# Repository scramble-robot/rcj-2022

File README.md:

# rcj-2022

This program made by scramble rcj team.

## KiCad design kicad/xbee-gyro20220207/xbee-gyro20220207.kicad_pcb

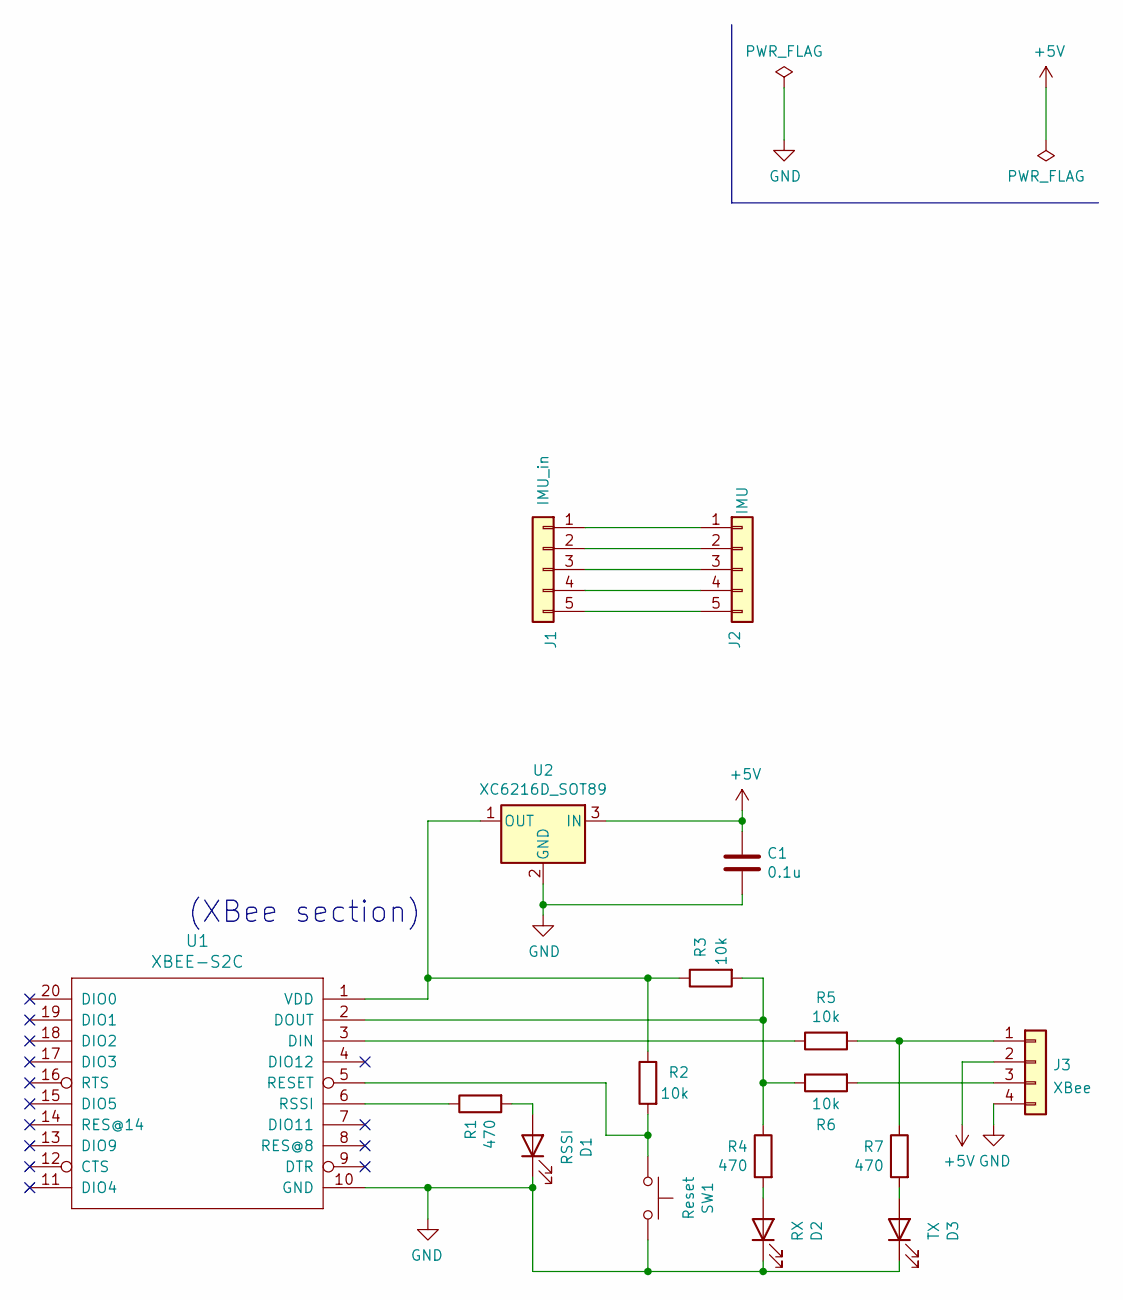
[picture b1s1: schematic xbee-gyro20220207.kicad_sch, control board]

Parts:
C1: 0.1u; C_0603_1608Metric_Pad1.08x0.95mm_HandSolder
D1: RSSI; LED_0603_1608Metric_Pad1.05x0.95mm_HandSolder
D2: RX; LED_0603_1608Metric_Pad1.05x0.95mm_HandSolder
D3: TX; LED_0603_1608Metric_Pad1.05x0.95mm_HandSolder
J1: IMU_in; PinSocket_1x05_P2.54mm_Vertical
J2: IMU; PinSocket_1x05_P2.54mm_Vertical
J3: XBee; PinSocket_1x04_P2.54mm_Vertical
R1, R4, R7: 470; R_0603_1608Metric_Pad0.98x0.95mm_HandSolder
R2, R3, R5, R6: 10k; R_0603_1608Metric_Pad0.98x0.95mm_HandSolder
SW1: Reset; THAU13-AB-R
U1: XBEE-S2C
U2: XC6216D_SOT89; SOT-89-3

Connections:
+5V: C1.1, J3.2, U2.3 (IN)
GND: C1.2, D1.1 (K), D2.1 (K), D3.1 (K), J3.4, SW1.2, U1.10 (GND), U2.2 (GND)
unnamed: D1.2 (A), R1.2
unnamed: D2.2 (A), R4.2
unnamed: D3.2 (A), R7.2
unnamed: J1.1, J2.1
unnamed: J1.2, J2.2
unnamed: J1.3, J2.3
unnamed: J1.4, J2.4
unnamed: J1.5, J2.5
unnamed: J3.1, R5.2, R7.1
unnamed: J3.3, R6.2
unnamed: R1.1, U1.6 (RSSI)
unnamed: R2.1, R3.1, U1.1 (VDD), U2.1 (OUT)
unnamed: R2.2, SW1.1, U1.5 (RESET)
unnamed: R3.2, R4.1, R6.1, U1.2 (DOUT)
unnamed: R5.1, U1.3 (DIN)

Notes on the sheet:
(XBee section)

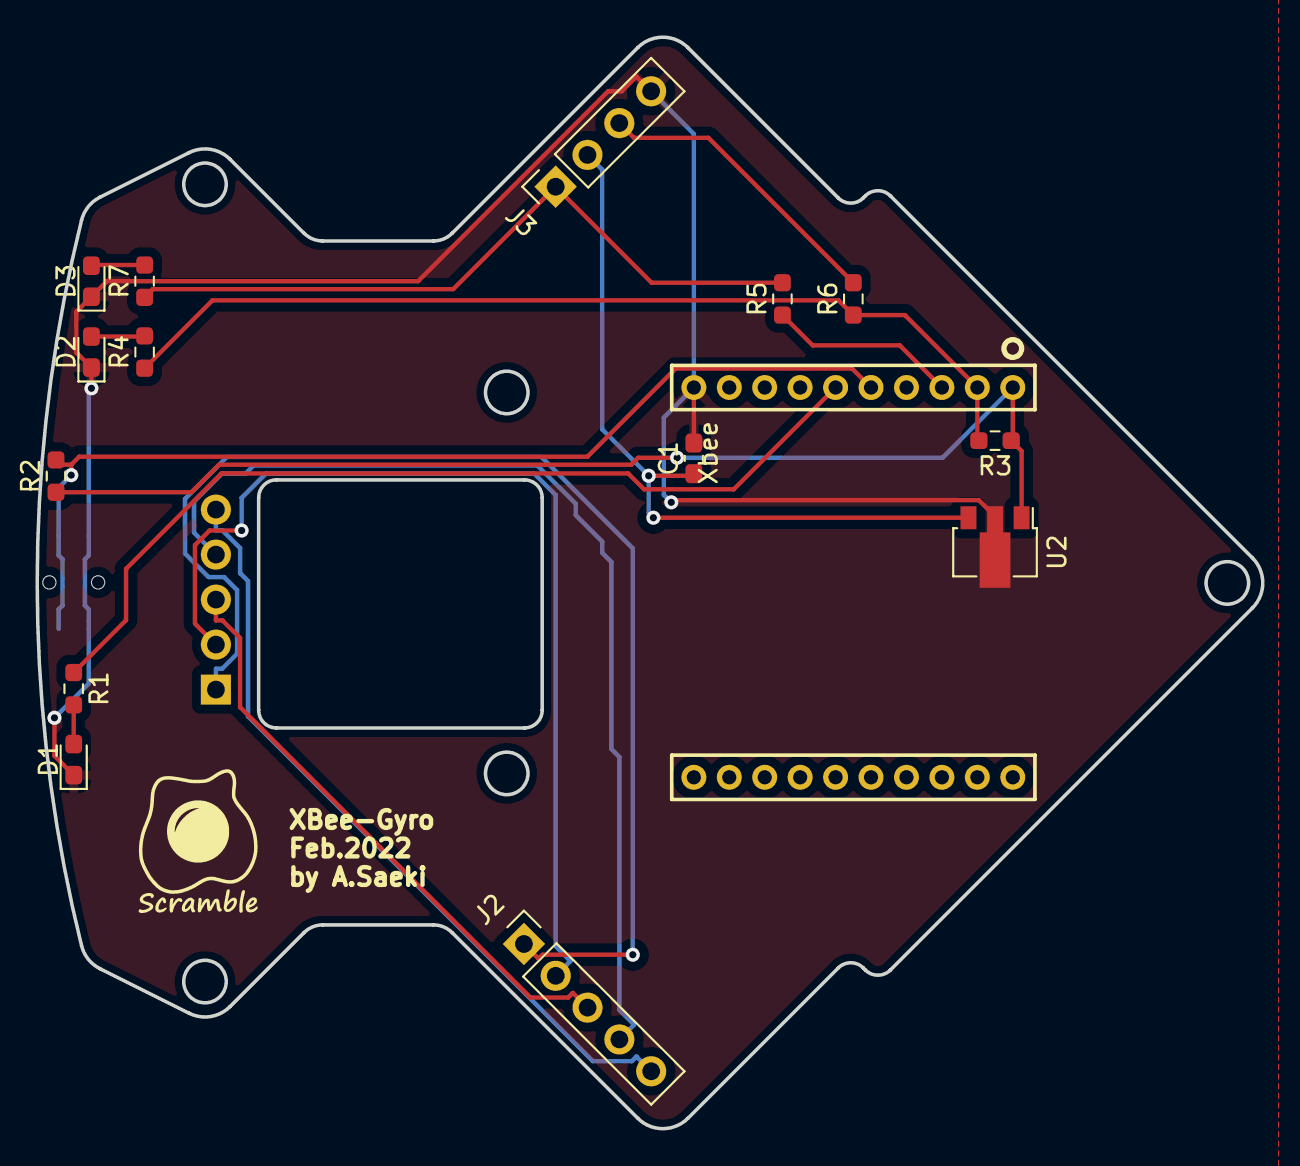
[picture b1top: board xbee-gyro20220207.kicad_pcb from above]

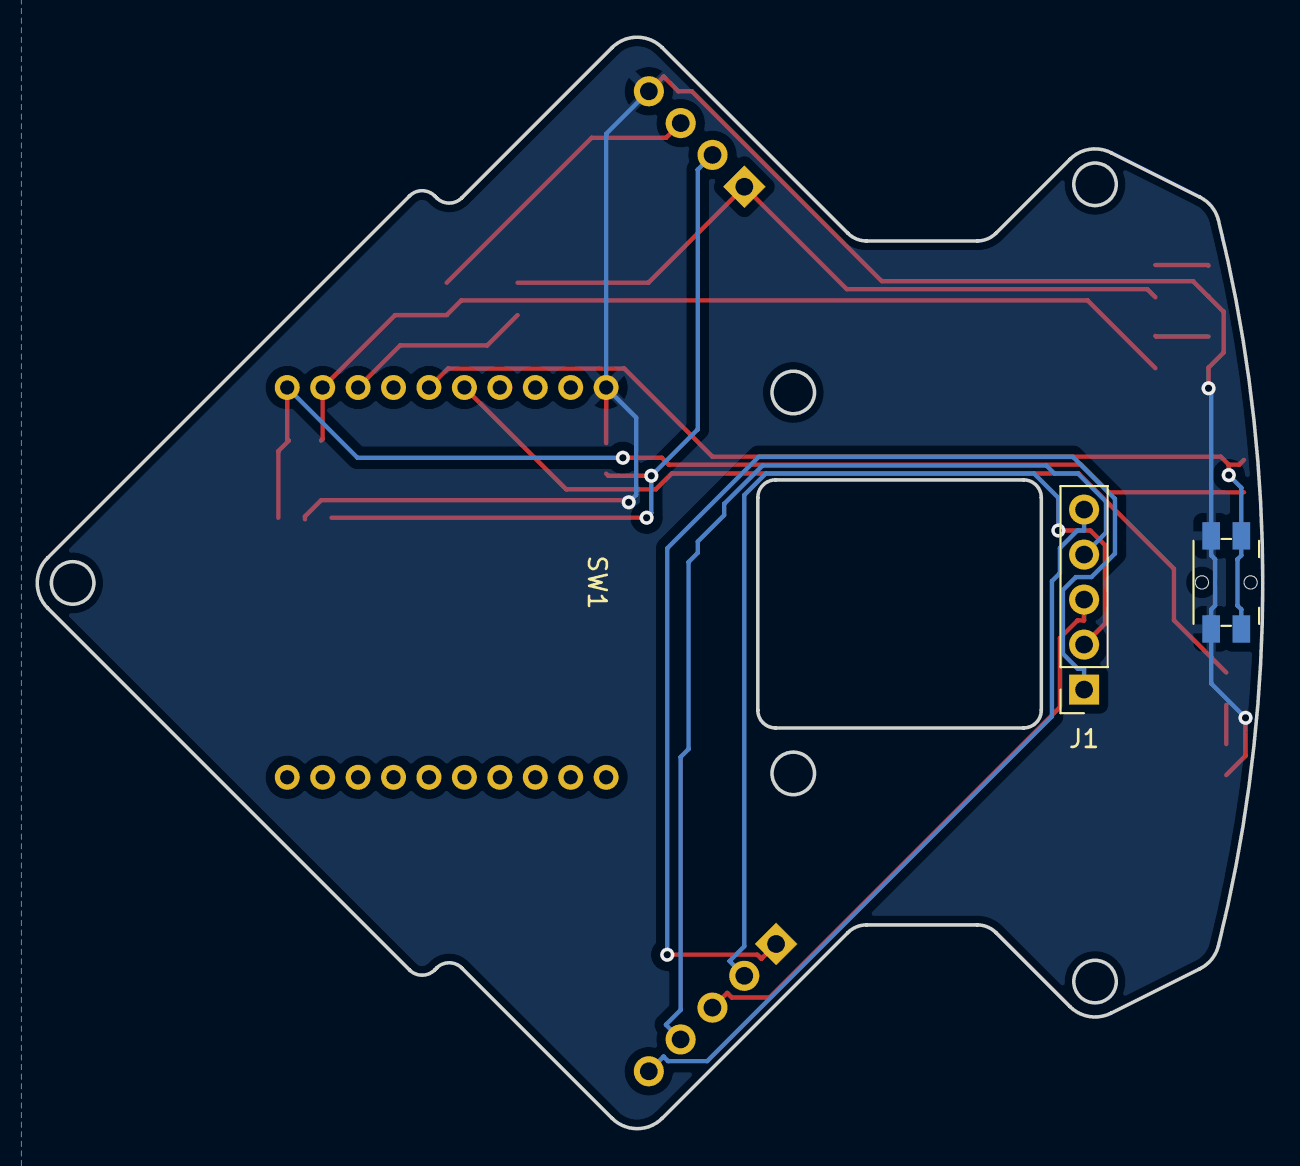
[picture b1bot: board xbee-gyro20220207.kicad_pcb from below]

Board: 2 copper layers, 69.2 x 61.6 mm, 17 parts (2 on the bottom side), 17 nets.

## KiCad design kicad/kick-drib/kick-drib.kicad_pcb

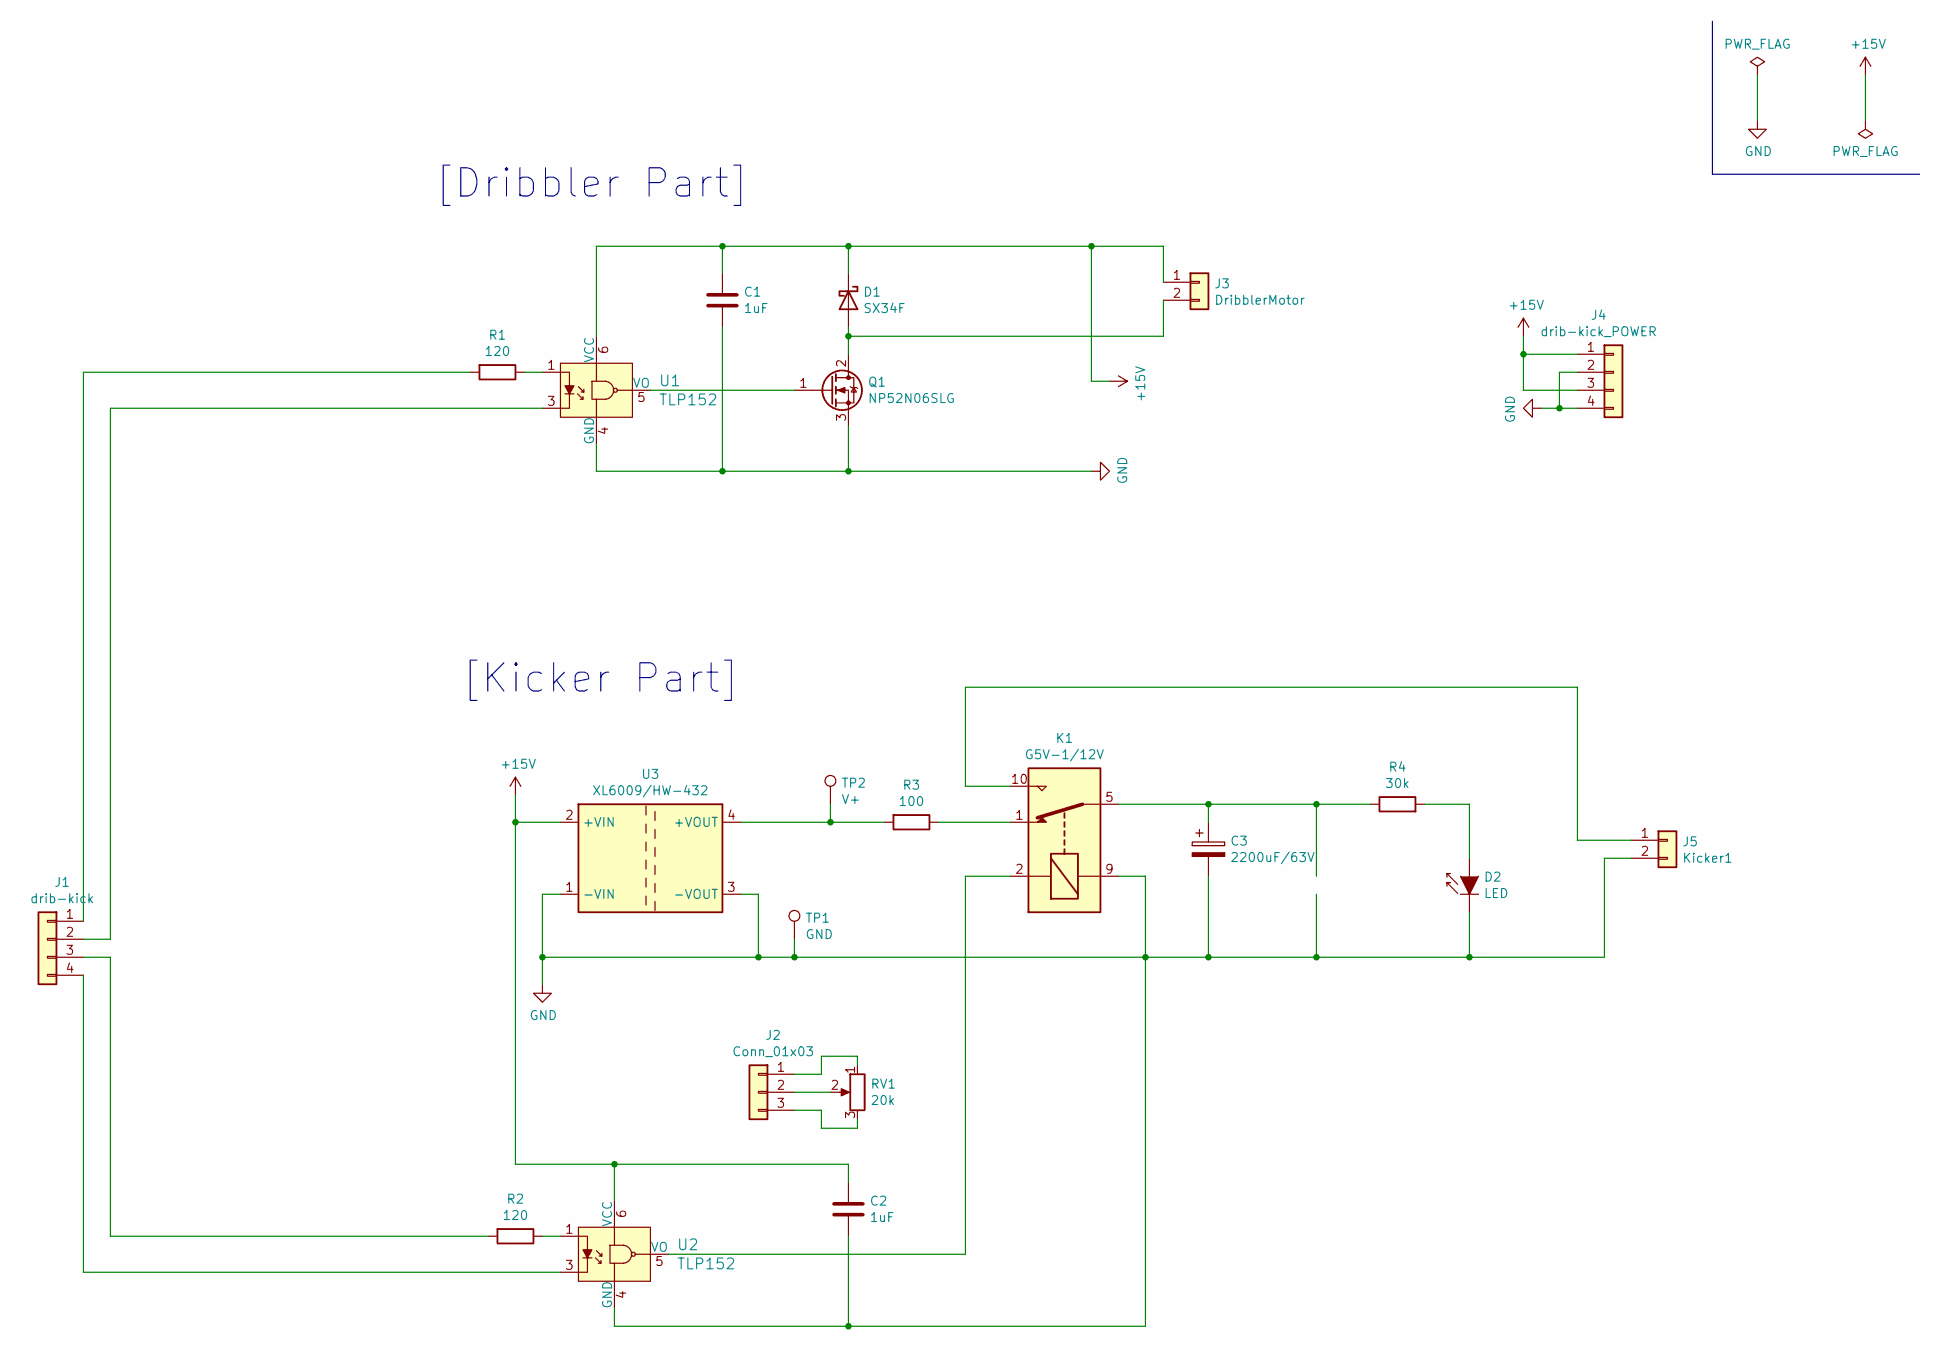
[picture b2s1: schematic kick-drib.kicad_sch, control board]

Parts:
C1, C2: 1uF; C_0603_1608Metric_Pad1.08x0.95mm_HandSolder
C3: 2200uF/63V; CP_Radial_D16.0mm_P7.50mm
D1: SX34F; D_SMA
D2: LED; LED_0603_1608Metric_Pad1.05x0.95mm_HandSolder
J1: drib-kick; PinHeader_1x04_P2.54mm_Vertical
J2: Conn_01x03; PinHeader_1x03_P2.54mm_Vertical
J3: DribblerMotor; JST_XH_B2B-XH-A_1x02_P2.50mm_Vertical
J4: drib-kick_POWER; PinHeader_1x04_P2.54mm_Vertical
J5: Kicker1; JST_XH_B2B-XH-A_1x02_P2.50mm_Vertical
K1: G5V-1/12V; Relay_SPDT_Omron_G5V-1
Q1: NP52N06SLG; TO-252-2
R1, R2: 120; R_0603_1608Metric_Pad0.98x0.95mm_HandSolder
R3: 100; R_Axial_DIN0411_L9.9mm_D3.6mm_P20.32mm_Horizontal
R4: 30k; R_Axial_DIN0204_L3.6mm_D1.6mm_P5.08mm_Horizontal
RV1: 20k; Trim-GF063X
TP1: GND; TestPoint_Loop_D2.60mm_Drill0.9mm_Beaded
TP2: V+; TestPoint_Loop_D2.60mm_Drill0.9mm_Beaded
U1, U2: TLP152
U3: XL6009/HW-432; XL6009_HW432

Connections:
+15V: C1.1, C2.1, D1.1 (K), J3.1, J4.1, J4.3, U1.6 (VCC), U2.6 (VCC), U3.2 (+VIN)
GND: C1.2, C2.2, C3.2, D2.1 (K), J4.2, J4.4, J5.2, K1.9, Q1.3 (S), TP1.1, U1.4 (GND), U2.4 (GND), U3.1 (-VIN), U3.3 (-VOUT)
unnamed: C3.1, K1.5, K1.6, R4.1
unnamed: D1.2 (A), J3.2, Q1.2 (D)
unnamed: D2.2 (A), R4.2
unnamed: J1.1, R1.2
unnamed: J1.2, U1.3
unnamed: J1.3, R2.2
unnamed: J1.4, U2.3
unnamed: J2.1, RV1.1
unnamed: J2.2, RV1.2
unnamed: J2.3, RV1.3
unnamed: J5.1, K1.10
unnamed: K1.1, R3.1
unnamed: K1.2, U2.5 (VO)
unnamed: Q1.1 (G), U1.5 (VO)
unnamed: R1.1, U1.1
unnamed: R2.1, U2.1
unnamed: R3.2, TP2.1, U3.4 (+VOUT)

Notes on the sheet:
[Kicker Part]
[Dribbler Part]

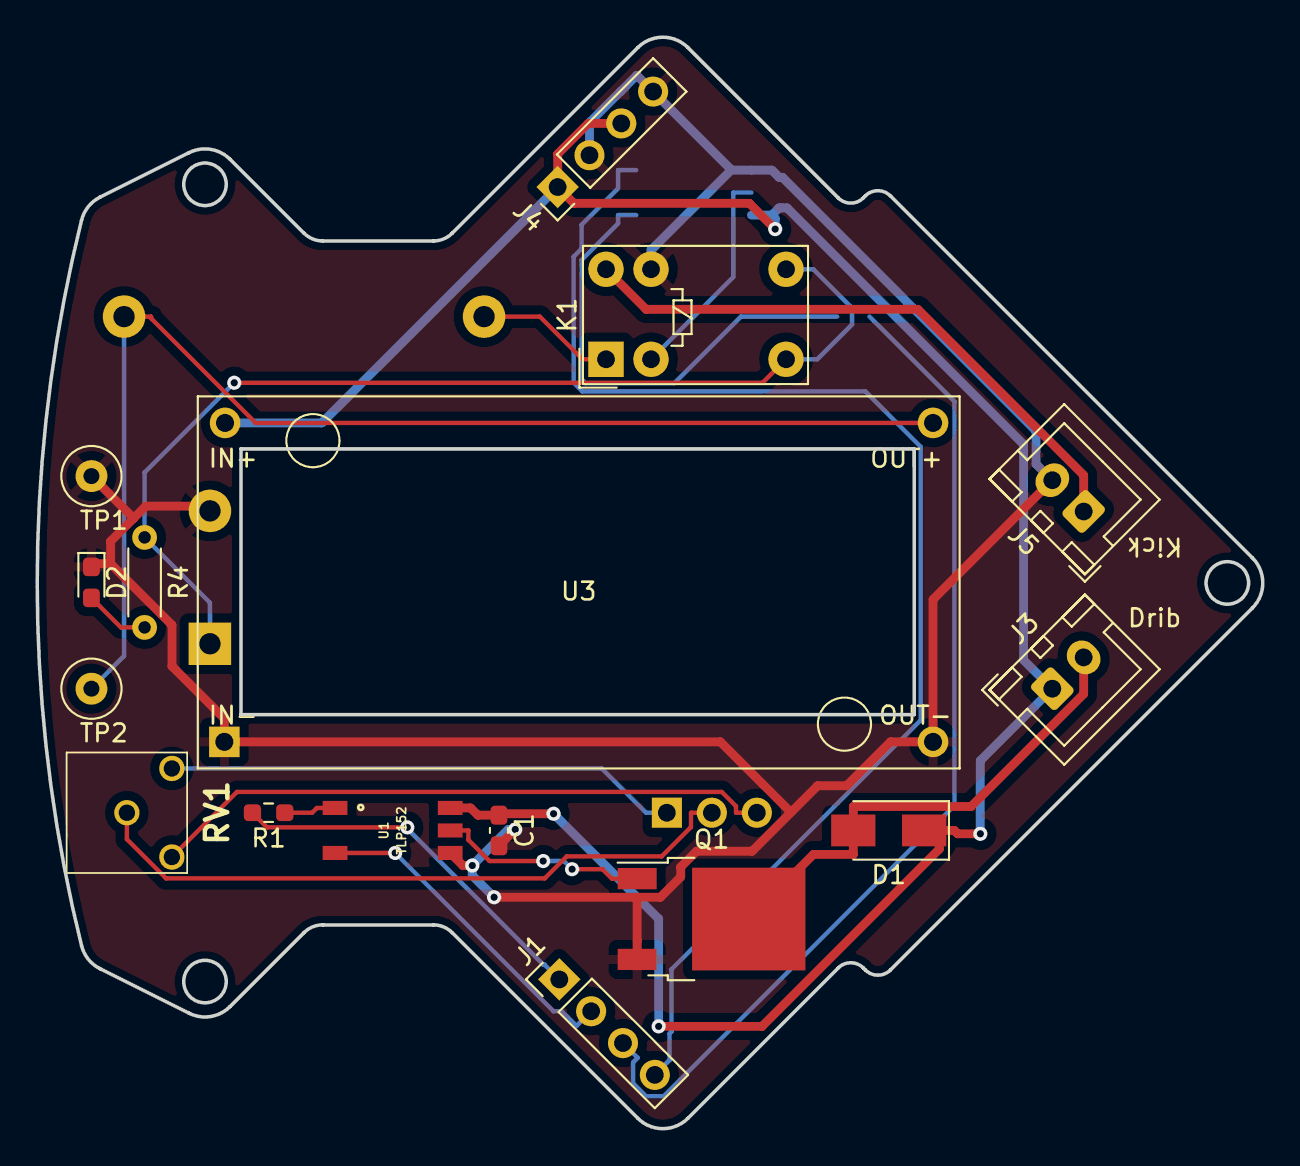
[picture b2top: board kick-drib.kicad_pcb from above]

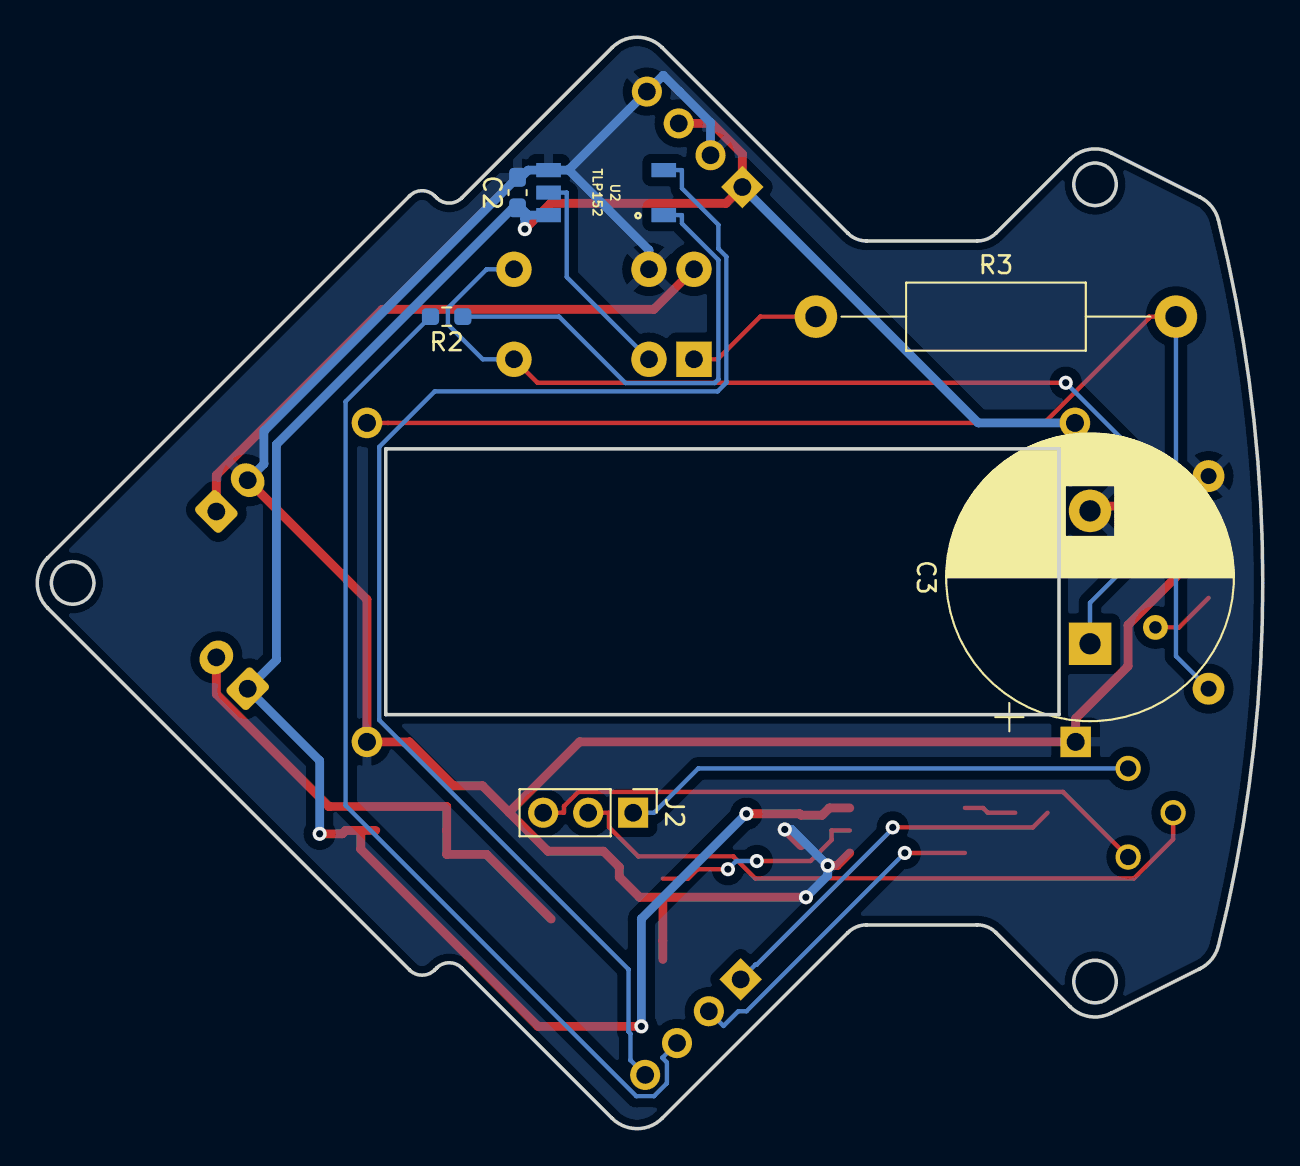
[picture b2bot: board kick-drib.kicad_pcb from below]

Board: 2 copper layers, 69.2 x 61.6 mm, 22 parts (6 on the bottom side), 19 nets.

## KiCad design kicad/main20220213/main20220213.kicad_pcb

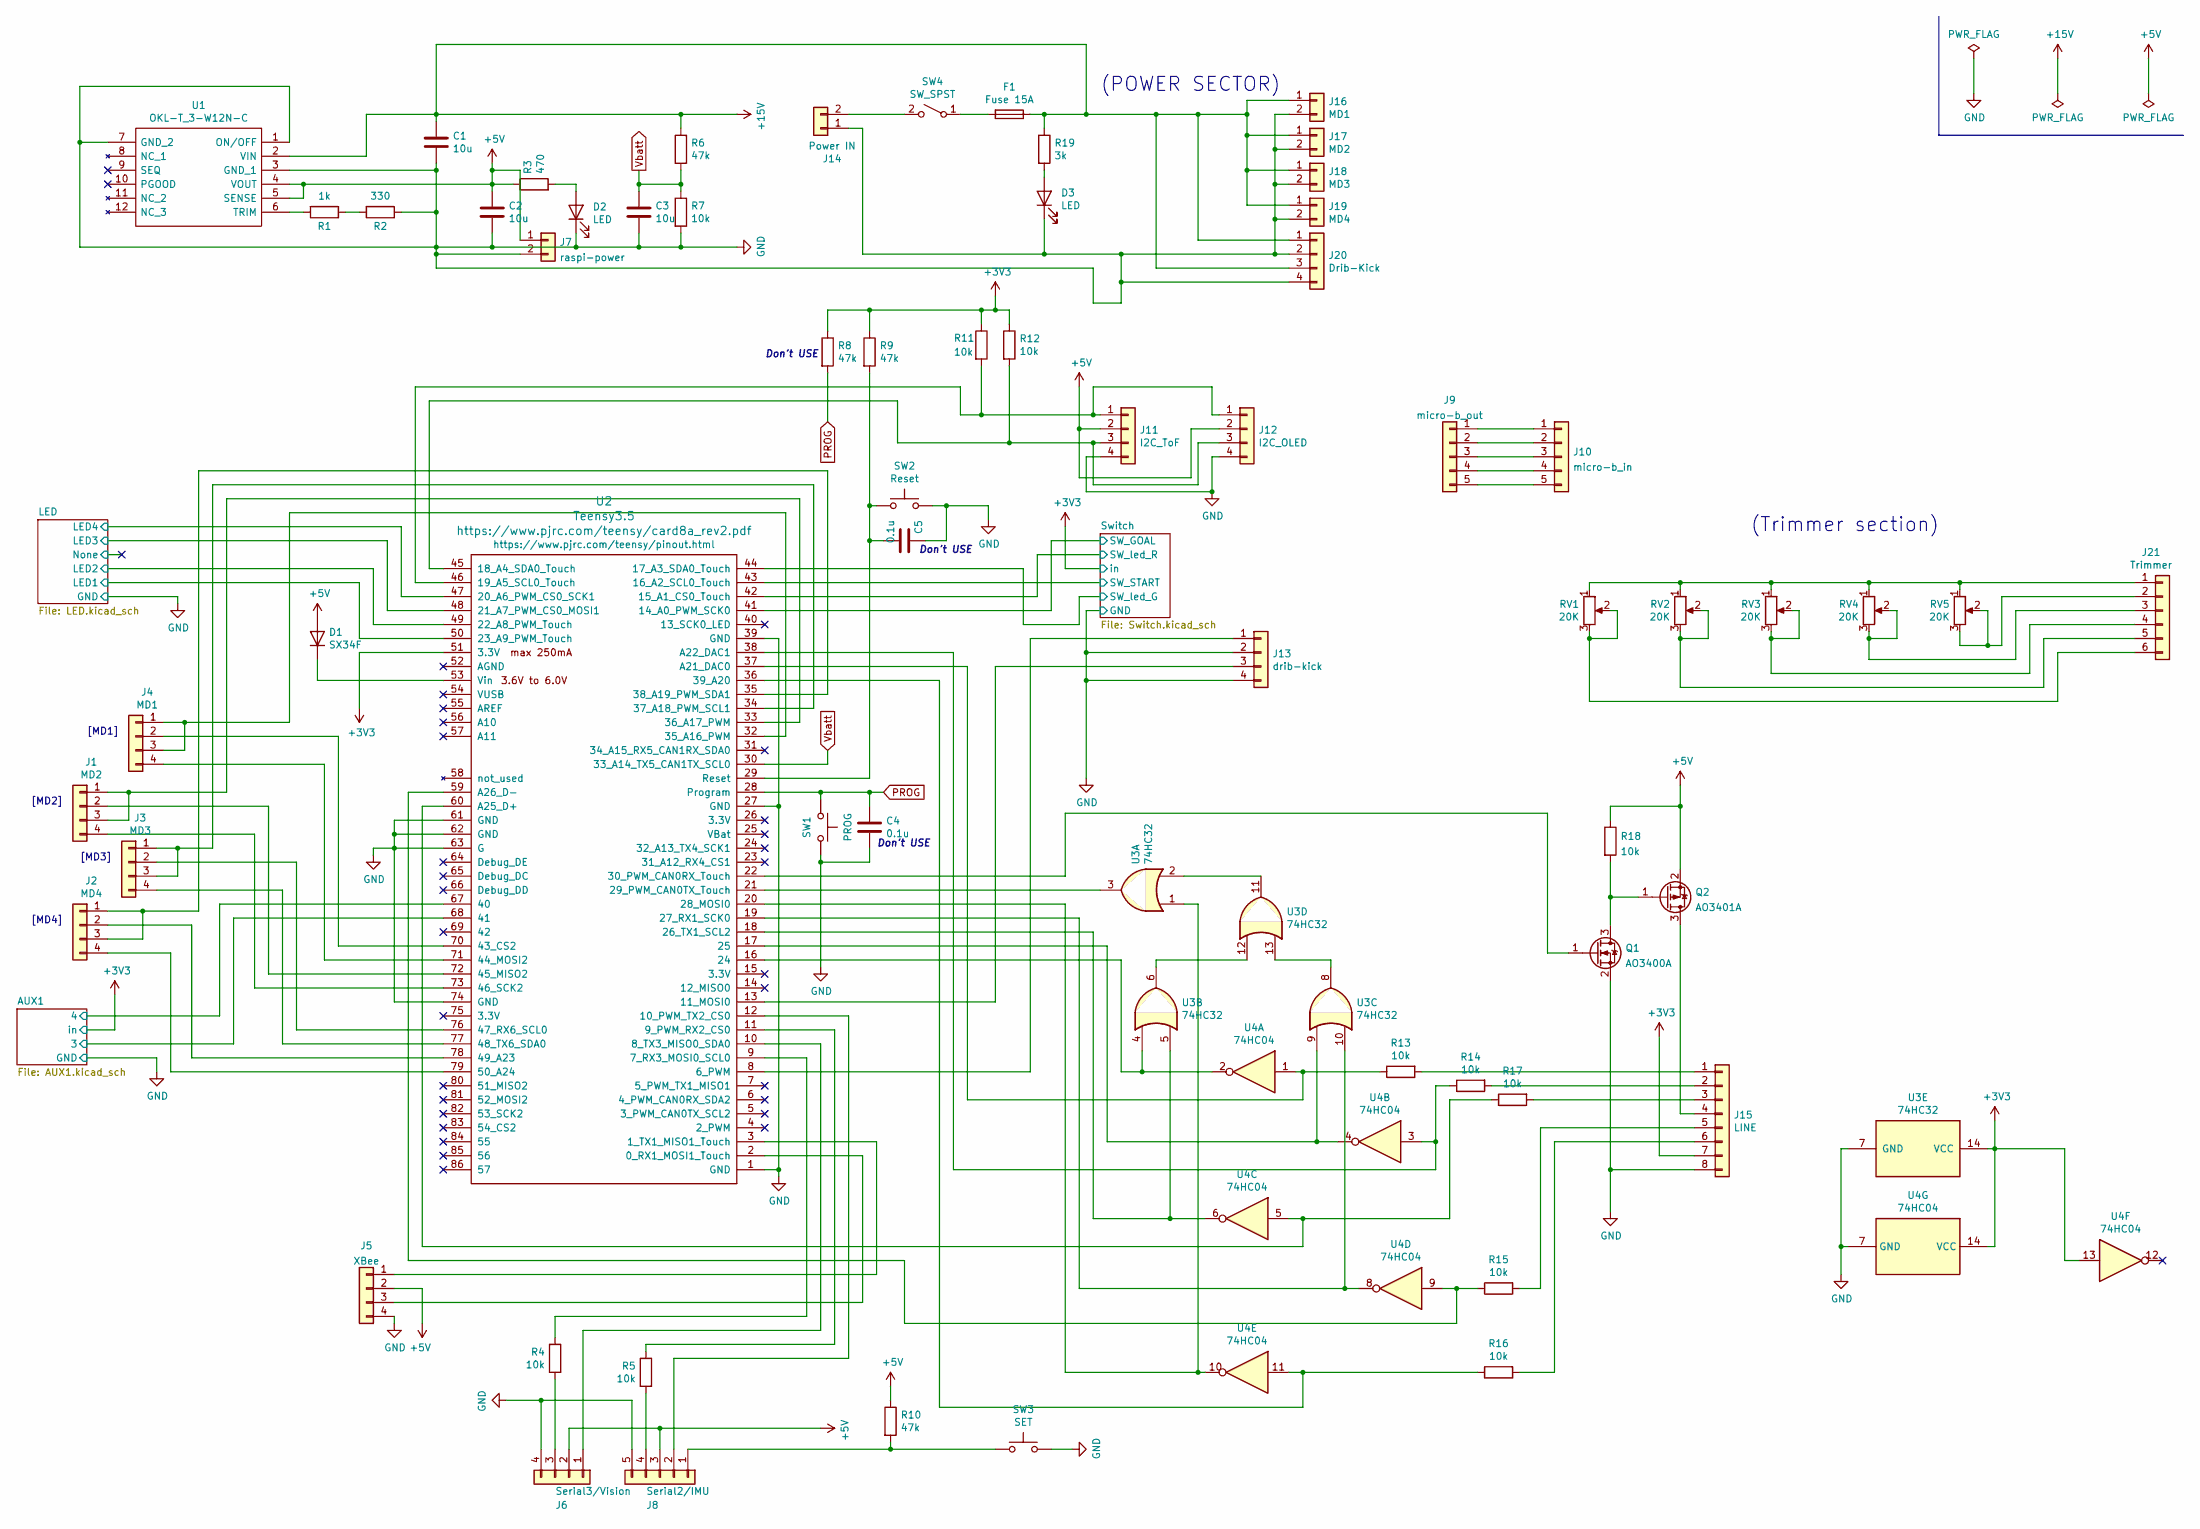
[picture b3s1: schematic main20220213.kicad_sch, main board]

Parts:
C1, C2, C3: 10u; C_0603_1608Metric_Pad1.08x0.95mm_HandSolder
C4, C5: 0.1u; C_0603_1608Metric_Pad1.08x0.95mm_HandSolder
D1: SX34F; D_SMA
D2, D3: LED; LED_SMLE13WBC8W1
F1: Fuse 15A; FUSE_20mm
J1: MD2; JSTS4B-ZRLFSN
J2: MD4; JSTS4B-ZRLFSN
J3: MD3; JSTS4B-ZRLFSN
J4: MD1; JSTS4B-ZRLFSN
J5: XBee; PinSocket_1x04_P2.54mm_Vertical
J6: Serial3/Vision; JSTB4B-ZR
J7: raspi-power; JST_PH_B2B-PH-K_1x02_P2.00mm_Vertical
J8: Serial2/IMU; PinSocket_1x05_P2.54mm_Vertical
J9: micro-b_out; PinHeader_1x05_P2.54mm_Vertical
J10: micro-b_in; PinHeader_1x05_P2.54mm_Vertical
J11: I2C_ToF; JSTS4B-ZRLFSN
J12: I2C_OLED; OLED
J13: drib-kick; PinSocket_1x04_P2.54mm_Vertical
J14: Power IN; AMASS_XT60-M_1x02_P7.20mm_Vertical
J15: LINE; JSTS8B-ZRLFSN
J16: MD1; JST_XH_B2B-XH-A_1x02_P2.50mm_Vertical
J17: MD2; JST_XH_B2B-XH-A_1x02_P2.50mm_Vertical
J18: MD3; JST_XH_B2B-XH-A_1x02_P2.50mm_Vertical
J19: MD4; JST_XH_B2B-XH-A_1x02_P2.50mm_Vertical
J20: Drib-Kick; PinSocket_1x04_P2.54mm_Vertical
J21: Trimmer; JSTS6B-ZRLFSN
Q1: AO3400A; SOT-23
Q2: AO3401A; SOT-23
R1: 1k; R_Axial_DIN0204_L3.6mm_D1.6mm_P5.08mm_Horizontal
R2: 330; R_Axial_DIN0204_L3.6mm_D1.6mm_P5.08mm_Horizontal
R3: 470; R_0603_1608Metric_Pad0.98x0.95mm_HandSolder
R4, R5, R7, R11, R12, R13, R14, R15, R16, R17, R18: 10k; R_0603_1608Metric_Pad0.98x0.95mm_HandSolder
R6, R8, R9, R10: 47k; R_0603_1608Metric_Pad0.98x0.95mm_HandSolder
R19: 3k; R_0603_1608Metric_Pad0.98x0.95mm_HandSolder
RV1, RV2, RV3, RV4, RV5: 20K; Trim-GF063P
SW1: PROG; TVAF06-A020B-R
SW2: Reset; THAU13-AB-R
SW3: SET; SW_PUSH_6mm
SW4: SW_SPST; SW_SPST_POWER
U1: OKL-T_3-W12N-C; OKL-T3-W12N-C; Manufacturer_Part_Number OKL-T/6-W12N-C; Mouser Part Number 580-OKL-T/6-W12N-C
U2: Teensy3.5; Teensy35_36_x
U3: 74HC32; SOP14W
U4: 74HC04; SOP14W

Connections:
+3V3: J15.7, R8.1, R9.1, R11.1, R12.1, U2.51 (3.3V), U3.14 (VCC), U4.13, U4.14 (VCC); also elsewhere on the board
+5V: C2.1, D1.2 (A), J5.2, J6.2, J7.1, J8.3, J11.2, J12.2, Q2.2 (S), R3.1, R10.1, R18.1, U1.4 (VOUT), U1.5 (SENSE)
+15V: C1.1, F1.1, J16.1, J17.1, J18.1, J19.1, J20.1, J20.3, R6.1, R19.1, U1.2 (VIN)
/LED/LED1: U2.50 (23_A9_PWM_Touch); also elsewhere on the board
/LED/LED2: U2.49 (22_A8_PWM_Touch); also elsewhere on the board
/LED/LED3: U2.48 (21_A7_PWM_CS0_MOSI1); also elsewhere on the board
/LED/LED4: U2.47 (20_A6_PWM_CS0_SCK1); also elsewhere on the board
/Switch/SW_GOAL: U2.41 (14_A0_PWM_SCK0); also elsewhere on the board
/Switch/SW_START: U2.43 (16_A2_SCL0_Touch); also elsewhere on the board
/Switch/SW_led_G: U2.44 (17_A3_SDA0_Touch); also elsewhere on the board
/Switch/SW_led_R: U2.42 (15_A1_CS0_Touch); also elsewhere on the board
GND: C1.2, C2.2, C3.2, C4.2, C5.1, D2.1 (K), D3.1 (K), J5.4, J6.4, J7.2, J8.5, J11.4, J12.4, J13.2, J13.4, J14.1, J15.8, J16.2, J17.2, J18.2, J19.2, J20.2, J20.4, Q1.2 (S), R2.1, R7.2, SW1.2, SW2.2, SW3.2, U1.1 (ON/OFF), U1.3 (GND_1), U1.7 (GND_2), U2.1 (GND), U2.27 (GND), U2.39 (GND), U2.61 (GND), U2.62 (GND), U2.63 (G), U2.74 (GND), U3.7 (GND), U4.7 (GND); also elsewhere on the board
unnamed: C5.2, R9.2, SW2.1, U2.29 (Reset)
unnamed: D1.1 (K), U2.53 (Vin)
unnamed: D2.2 (A), R3.2
unnamed: D3.2 (A), R19.2
unnamed: F1.2, SW4.1 (A)
unnamed: J1.1, J1.3, U2.33 (36_A17_PWM)
unnamed: J1.2, U2.72 (45_MISO2)
unnamed: J1.4, U2.73 (46_SCK2)
unnamed: J2.1, J2.3, U2.35 (38_A19_PWM_SDA1)
unnamed: J2.2, U2.78 (49_A23)
unnamed: J2.4, U2.79 (50_A24)
unnamed: J3.1, J3.3, U2.34 (37_A18_PWM_SCL1)
unnamed: J3.2, U2.76 (47_RX6_SCL0)
unnamed: J3.4, U2.77 (48_TX6_SDA0)
unnamed: J4.1, J4.3, U2.32 (35_A16_PWM)
unnamed: J4.2, U2.70 (43_CS2)
unnamed: J4.4, U2.71 (44_MOSI2)
unnamed: J5.1, U2.3 (1_TX1_MISO1_Touch)
unnamed: J5.3, U2.2 (0_RX1_MOSI1_Touch)
unnamed: J6.1, U2.10 (8_TX3_MISO0_SDA0)
unnamed: J6.3, R4.2
unnamed: J8.1, R10.2, SW3.1
unnamed: J8.2, U2.12 (10_PWM_TX2_CS0)
unnamed: J8.4, R5.2
unnamed: J9.1, J10.1
unnamed: J9.2, J10.2
unnamed: J9.3, J10.3
unnamed: J9.4, J10.4
unnamed: J9.5, J10.5
unnamed: J11.1, J12.1, R11.2, U2.46 (19_A5_SCL0_Touch)
unnamed: J11.3, J12.3, R12.2, U2.45 (18_A4_SDA0_Touch)
unnamed: J13.1, U2.8 (6_PWM)
unnamed: J13.3, U2.13 (11_MOSI0)
unnamed: J14.2, SW4.2 (B)
unnamed: J15.1, R13.2
unnamed: J15.2, R14.2
unnamed: J15.3, R17.2
unnamed: J15.4, Q2.3 (D)
unnamed: J15.5, R15.2
unnamed: J15.6, R16.2
unnamed: J21.1, RV1.1, RV2.1, RV3.1, RV4.1, RV5.1
unnamed: J21.2, RV5.2, RV5.3
unnamed: J21.3, RV4.2, RV4.3
unnamed: J21.4, RV3.2, RV3.3
unnamed: J21.5, RV2.2, RV2.3
unnamed: J21.6, RV1.2, RV1.3
unnamed: Q1.1 (G), U2.22 (30_PWM_CAN0RX_Touch)
unnamed: Q1.3 (D), Q2.1 (G), R18.2
unnamed: R1.1, R2.2
unnamed: R1.2, U1.6 (TRIM)
unnamed: R4.1, U2.9 (7_RX3_MOSI0_SCL0)
unnamed: R5.1, U2.11 (9_PWM_RX2_CS0)
unnamed: R13.1, U2.37 (A21_DAC0), U4.1
unnamed: R14.1, U2.38 (A22_DAC1), U4.3
unnamed: R15.1, U2.59 (A26_D-), U4.9
unnamed: R16.1, U2.36 (39_A20), U4.11
unnamed: R17.1, U2.60 (A25_D+), U4.5
unnamed: U2.16 (24), U3.4, U4.2
unnamed: U2.17 (25), U3.9, U4.4
unnamed: U2.18 (26_TX1_SCL2), U3.5, U4.6
unnamed: U2.19 (27_RX1_SCK0), U3.10, U4.8
unnamed: U2.20 (28_MOSI0), U3.1, U4.10
unnamed: U2.21 (29_PWM_CAN0TX_Touch), U3.3
unnamed: U3.2, U3.11
unnamed: U3.6, U3.12
unnamed: U3.8, U3.13
PROG: C4.1, R8.2, SW1.1, U2.28 (Program)
Vbatt: C3.1, R6.2, R7.1, U2.30 (33_A14_TX5_CAN1TX_SCL0)

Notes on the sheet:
(POWER SECTOR)
(Trimmer section)
Don't USE
[MD3]
[MD2]
[MD1]
[MD4]

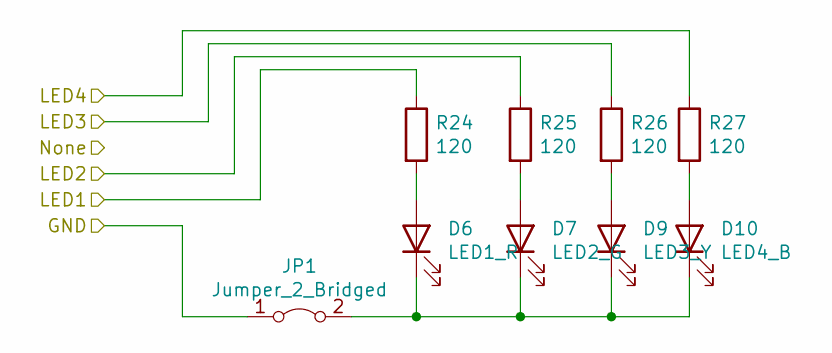
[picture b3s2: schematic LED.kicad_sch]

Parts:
D6: LED1_R; LED_SMLE13WBC8W1
D7: LED2_G; LED_SMLE13WBC8W1
D9: LED3_Y; LED_SMLE13WBC8W1
D10: LED4_B; LED_SMLE13WBC8W1
JP1: Jumper_2_Bridged; PinHeader_1x02_P1.27mm_Vertical
R24, R25, R26, R27: 120; R_0603_1608Metric_Pad0.98x0.95mm_HandSolder

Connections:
+3V3: R24.1, R25.1; also elsewhere on the board
/Switch/SW_led_G: R27.1; also elsewhere on the board
/Switch/SW_led_R: R26.1; also elsewhere on the board
GND: JP1.1 (A); also elsewhere on the board
unnamed 16: D6.1 (K), D7.1 (K), D9.1 (K), D10.1 (K), JP1.2 (B); also elsewhere on the board
unnamed 72: D9.2 (A), R26.2; also elsewhere on the board
unnamed 73: D10.2 (A), R27.2; also elsewhere on the board

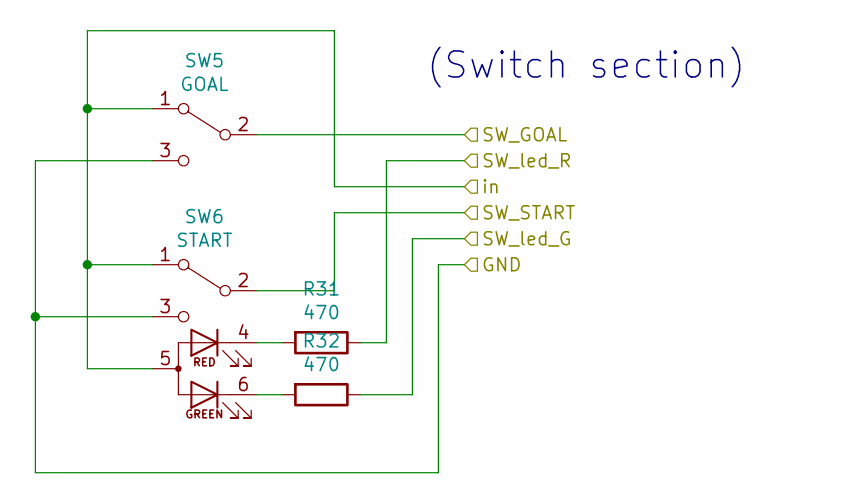
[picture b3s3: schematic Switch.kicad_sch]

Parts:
R31, R32: 470; R_0603_1608Metric_Pad0.98x0.95mm_HandSolder
SW5: GOAL; MFS101D-14-Z
SW6: START; SW_NKK_B-12CCPRM

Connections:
+3V3: SW5.1 (A), SW6.1 (A), SW6.5 (A); also elsewhere on the board
/Switch/SW_GOAL: SW5.2 (B); also elsewhere on the board
/Switch/SW_START: SW6.2 (B); also elsewhere on the board
GND: SW5.3 (C), SW6.3 (C); also elsewhere on the board
unnamed 72: R31.2, SW6.4 (KR); also elsewhere on the board
unnamed 73: R32.2, SW6.6 (KG); also elsewhere on the board

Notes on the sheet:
(Switch section)

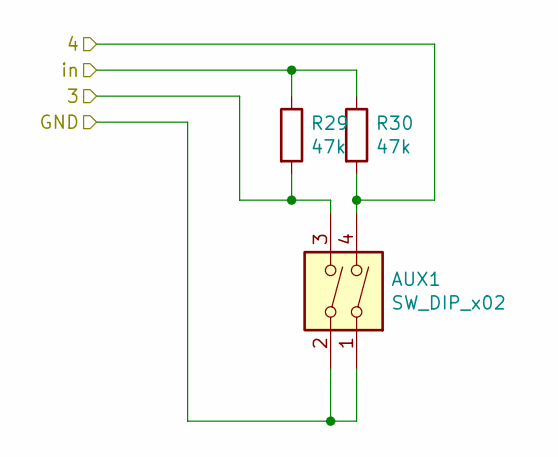
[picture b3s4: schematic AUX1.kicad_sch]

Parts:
AUX1: SW_DIP_x02; SW_DIP_SPSTx02_Slide_9.78x7.26mm_W7.62mm_P2.54mm
R29, R30: 47k; R_0603_1608Metric_Pad0.98x0.95mm_HandSolder

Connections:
GND: AUX1.1, AUX1.2; also elsewhere on the board
unnamed: R29.1, R30.1

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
